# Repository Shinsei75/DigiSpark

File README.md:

# DigiSpark
DigiSpark for home use.

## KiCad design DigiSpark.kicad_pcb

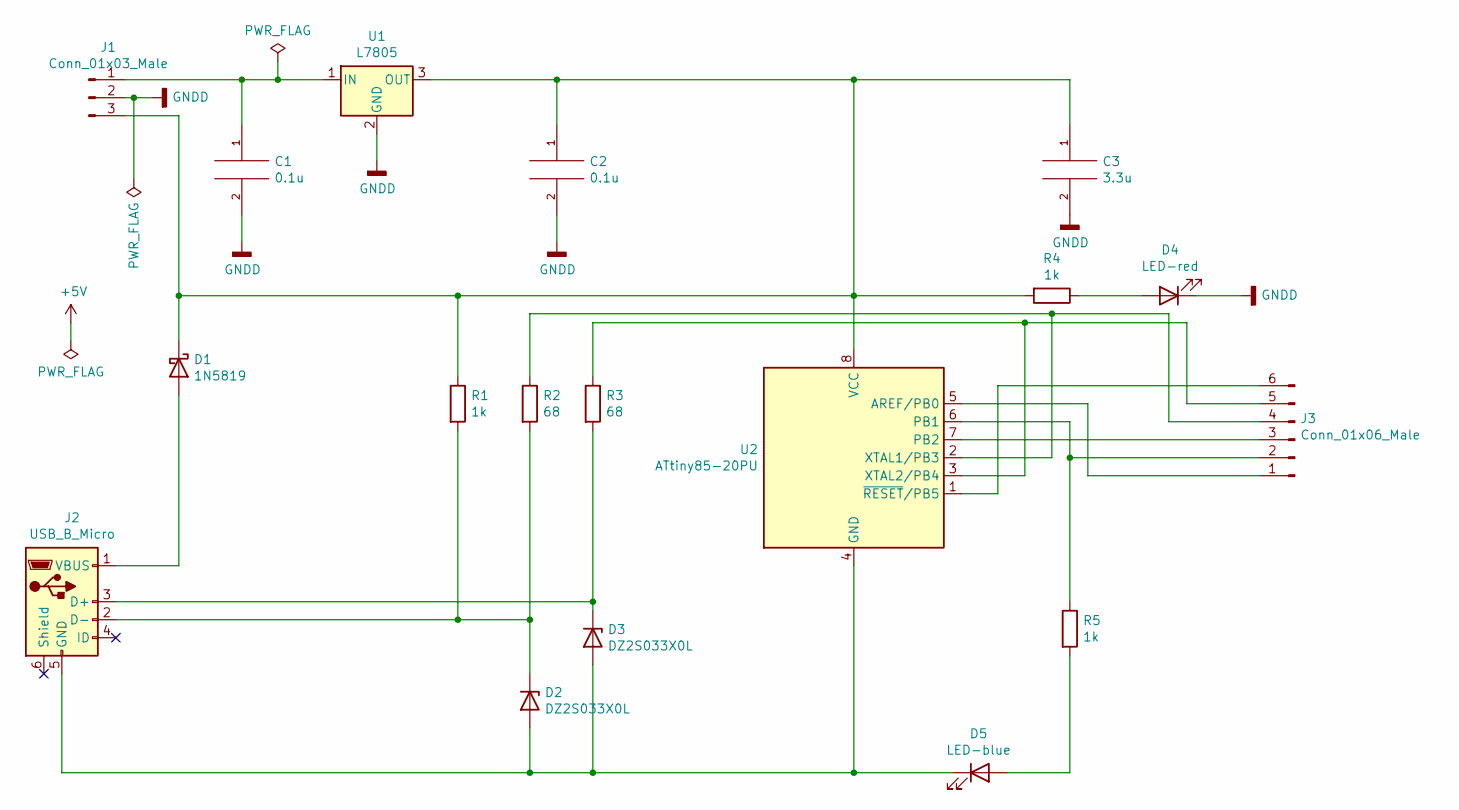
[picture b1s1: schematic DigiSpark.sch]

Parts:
C1, C2: 0.1u; C_0805_2012Metric
C3: 3.3u; C_0805_2012Metric
D1: 1N5819; D_DO-41_SOD81_P10.16mm_Horizontal
D2, D3: DZ2S033X0L; D_SOD-523
D4: LED-red; LED_0805_2012Metric
D5: LED-blue; LED_0805_2012Metric
J1: Conn_01x03_Male; PinHeader_1x03_P2.54mm_Vertical
J2: USB_B_Micro; USB_Micro-AB_Molex_47590-0001
J3: Conn_01x06_Male; PinHeader_1x06_P2.54mm_Vertical
R1, R4, R5: 1k; R_0805_2012Metric
R2, R3: 68; R_0805_2012Metric
U1: L7805; TO-263-3_TabPin4
U2: ATtiny85-20PU; DIP-8_W7.62mm

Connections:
GNDD: C1.2, C2.2, C3.2, D4.1 (K), J1.2, U1.2 (GND)
unnamed: C1.1, J1.1, U1.1 (IN)
unnamed: C2.1, C3.1, D1.1 (K), J1.3, R1.1, R4.2, U1.3 (OUT), U2.8 (VCC)
unnamed: D1.2 (A), J2.1 (VBUS)
unnamed: D2.1 (K), J2.2 (D-), R1.2, R2.2
unnamed: D2.2 (A), D3.2 (A), D5.1 (K), J2.5 (GND), U2.4 (GND)
unnamed: D3.1 (K), J2.3 (D+), R3.2
unnamed: D4.2 (A), R4.1
unnamed: D5.2 (A), R5.2
unnamed: J3.1, U2.5 (AREF/PB0)
unnamed: J3.2, R5.1, U2.6 (PB1)
unnamed: J3.3, U2.7 (PB2)
unnamed: J3.4, R2.1, U2.2 (XTAL1/PB3)
unnamed: J3.5, R3.1, U2.3 (XTAL2/PB4)
unnamed: J3.6, U2.1 (~RESET~/PB5)

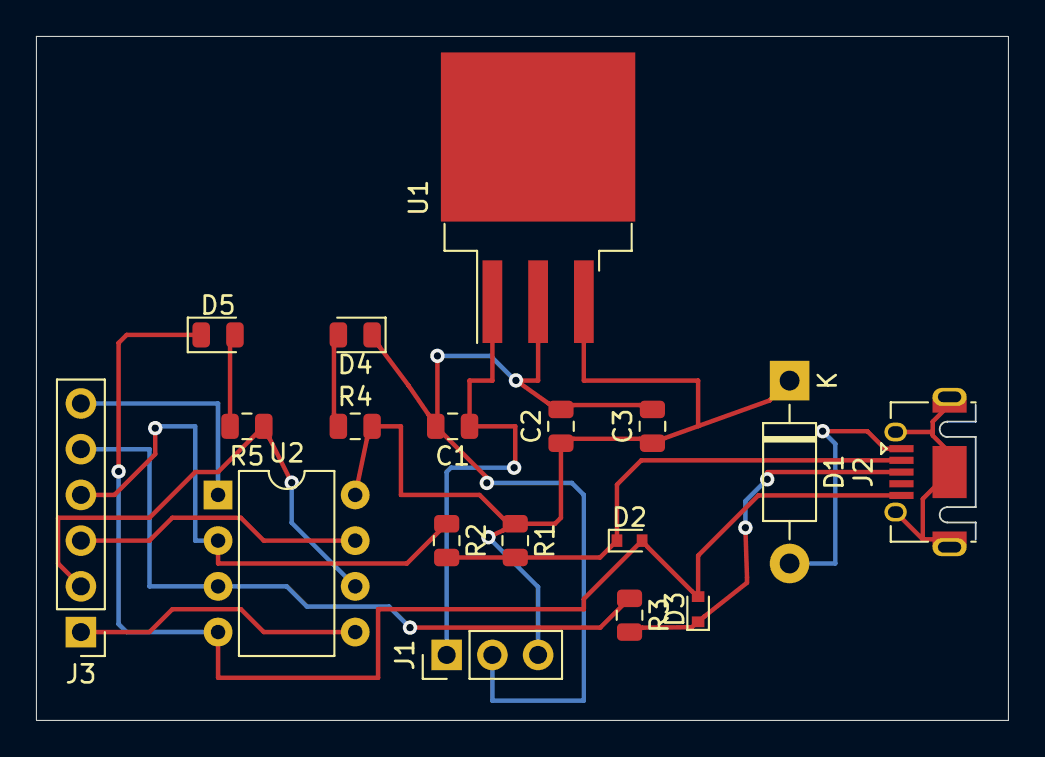
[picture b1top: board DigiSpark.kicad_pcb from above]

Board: 2 copper layers, 54.0 x 38.0 mm, 18 parts (0 on the bottom side), 15 nets.
